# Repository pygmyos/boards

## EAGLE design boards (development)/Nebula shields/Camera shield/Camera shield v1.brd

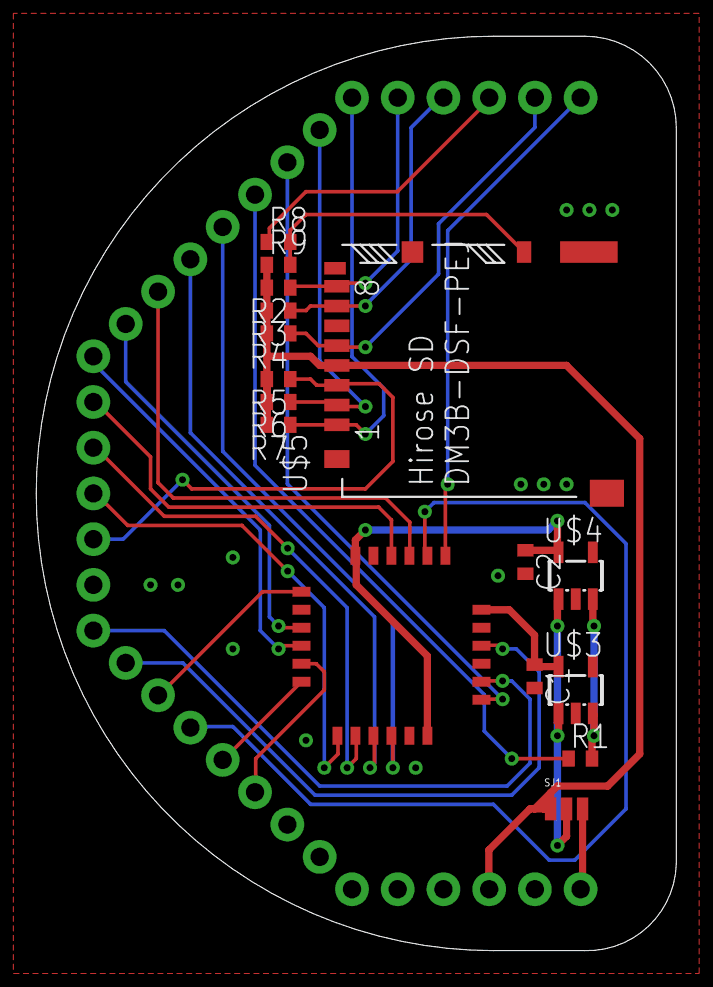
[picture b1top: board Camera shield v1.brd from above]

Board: 2 copper layers, 35.6 x 50.8 mm, 19 parts (1 on the bottom side), 32 nets.

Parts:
C1, C2: 1uF; C0402
INFO2: Evan Teitelman and Warren D Greenway; %CC-NC-SA
LOGO1: #PYGMYLOGONORMAL; #PYGMYLOGO
NEBULA1: #NEBULAPTH; #NEBULA-PTH@1
R1: 1K; R0402
R2, R3, R4, R5, R6, R7: 47K; R0402
R8: 10K; R0402
R9: 100K; R0402
SJ1: SJ_3
U$2: TCM8240MD
U$3, U$4: NCP500; SOT23-5L
U$5: HIROSE-SDCARD-DM3B-DSF-PEJ

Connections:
3.3V: NEBULA1.3.3V, R2.2, R3.2, R4.2, R5.2, R6.2, R7.2, R9.1, SJ1.1, U$5.P$4
BAT: NEBULA1.BAT, SJ1.3
CLK: NEBULA1.COM1_TX, R4.1, U$5.P$5
CMD: NEBULA1.COM2_TX, R5.1, U$5.P$3
D0: NEBULA1.A2, U$2.P4
D1: NEBULA1.A3, U$2.P3
D2: NEBULA1.A4, U$2.P2
D3: NEBULA1.A5, U$2.P1
D4: NEBULA1.A6, U$2.P24
D5: NEBULA1.A7, U$2.P23
D6: NEBULA1.D1, U$2.P22
D7: NEBULA1.D2, U$2.P21
DAT0: NEBULA1.T0, R3.1, U$5.P$7
DAT1: NEBULA1.T1, R2.1, U$5.P$8
DAT2: NEBULA1.T2, R7.1, U$5.P$1
DAT3: NEBULA1.T3, R6.1, U$5.P$2
DCLK: NEBULA1.TA0, U$2.P19
ENABLE: NEBULA1.A1, R1.1
EXTCLK: NEBULA1.MCO, U$2.P13
GND: C1.2, C2.2, NEBULA1.GND1, NEBULA1.GND2, NEBULA1.GND3, NEBULA1.GND4, NEBULA1.GND5, U$2.P5, U$2.P9, U$2.P11, U$2.P17, U$2.P20, U$3.2, U$4.2, U$5.P$6, U$5.P$9, U$5.P$12, U$5.P$13, U$5.P$14
HBLK: NEBULA1.D3, U$2.P15
INSERT: NEBULA1.COM1_RX, R8.1
unnamed: R1.2, U$3.3, U$4.3
unnamed: SJ1.2, U$3.1, U$4.1
unnamed: R8.2, R9.2, U$5.P$11
RST: NEBULA1.A0, U$2.P7
SCL: NEBULA1.DAC1, U$2.P8
SDA: NEBULA1.DAC2, U$2.P10
STROBE: NEBULA1.TA1, U$2.P14
VBLK: NEBULA1.D0, U$2.P16
VCCIO: C1.1, U$2.P12, U$3.5
VDD: C2.1, U$2.P6, U$2.P18, U$4.5

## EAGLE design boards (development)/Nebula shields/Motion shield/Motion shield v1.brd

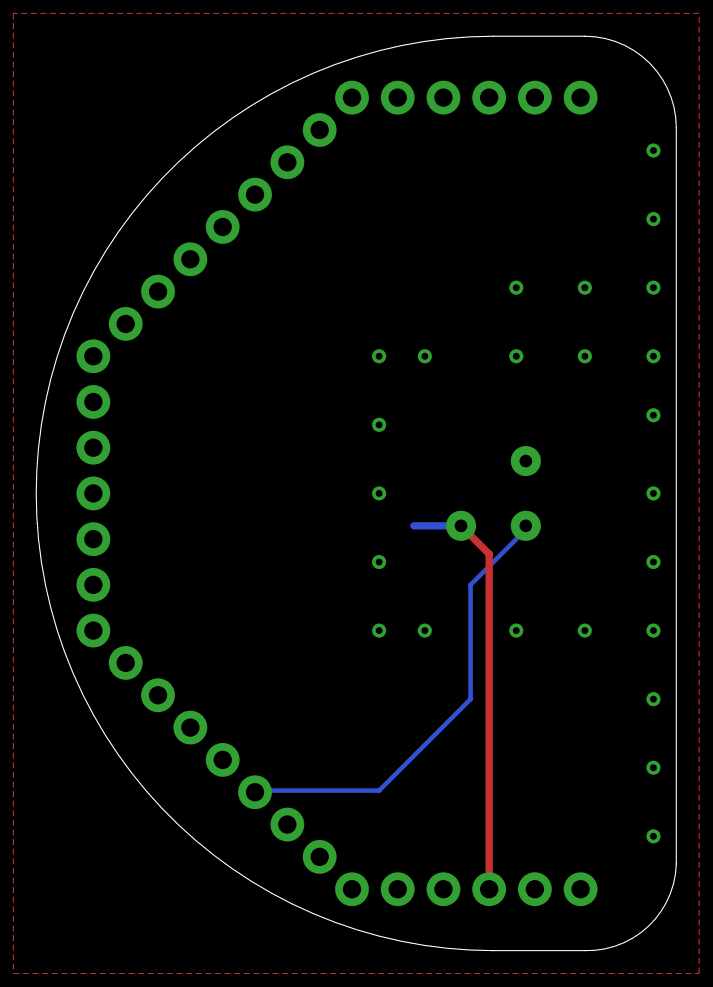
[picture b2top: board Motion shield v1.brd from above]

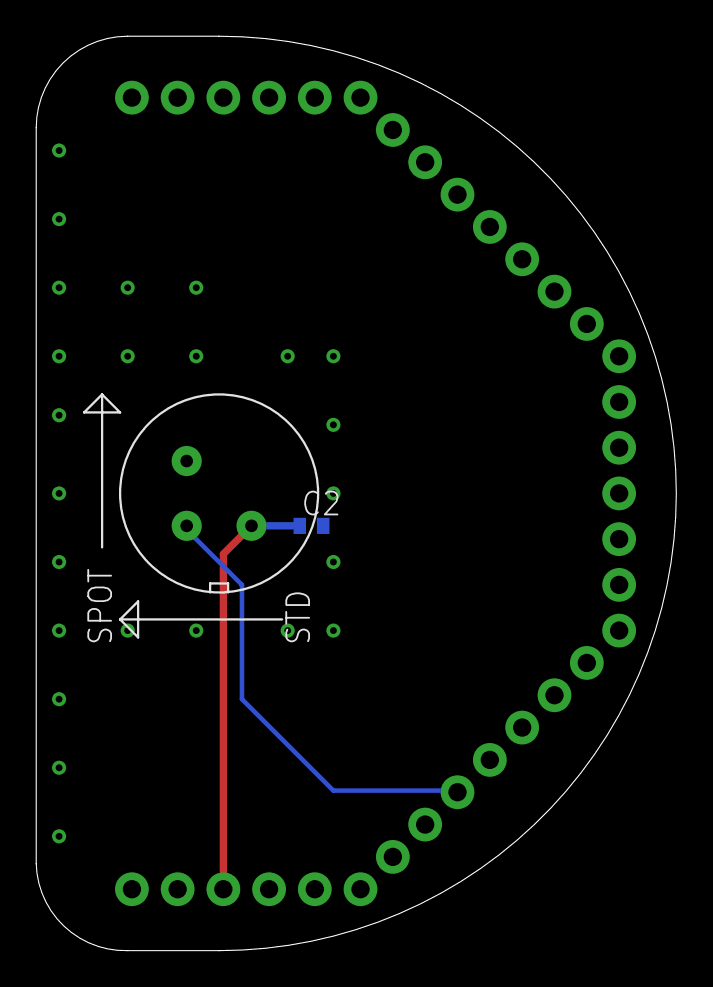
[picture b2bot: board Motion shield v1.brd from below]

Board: 2 copper layers, 35.6 x 50.8 mm, 5 parts (3 on the bottom side), 3 nets.

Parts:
C2: 0.1uF; C0402
INFO2: Warren D Greenway and Evan Teitelman; %CC-NC-SA
LOGO1: #PYGMYLOGONORMAL; #PYGMYLOGO
NEBULA1: #NEBULAPTH; #NEBULA-PTH@1
U2: PANASONIC-AMN41122

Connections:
3.3V: C2.1, NEBULA1.3.3V, U2.VCC
GND: C2.2, NEBULA1.GND1, NEBULA1.GND2, NEBULA1.GND3, NEBULA1.GND4, NEBULA1.GND5, U2.GND
SENSOR: NEBULA1.A7, U2.OUT

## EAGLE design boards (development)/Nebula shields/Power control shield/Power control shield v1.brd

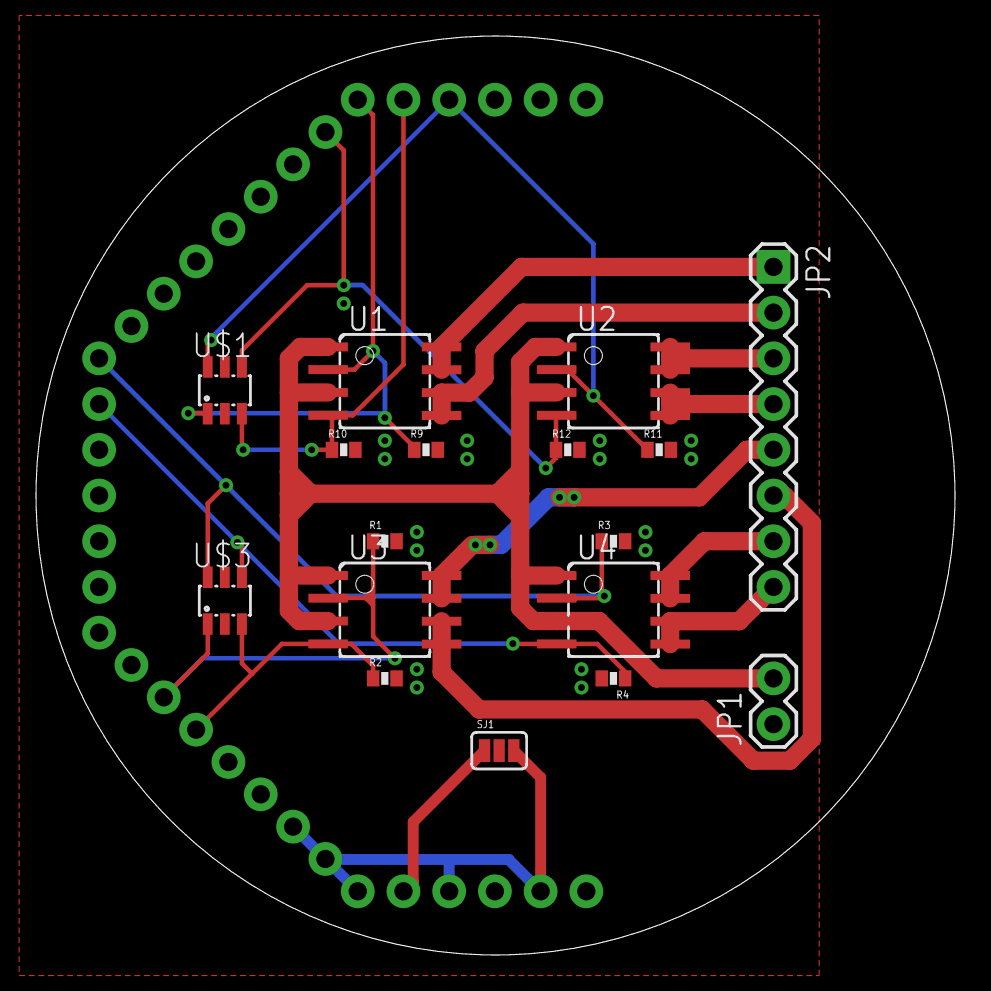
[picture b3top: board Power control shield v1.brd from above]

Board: 2 copper layers, 51.1 x 51.1 mm, 21 parts (1 on the bottom side), 20 nets.

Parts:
INFO2: Evan Teitelman and Warren D Greenway; %CC-NC-SA
JP1: 1X02
JP2: 1X08
LOGO1: #LOGOA-THICK
NEBULA1: #NEBULAPTH; #NEBULA-PTH
NEBULAPART1: #NEBULA-PARTLABELS-BOTTOM; #NEBULA-LABELS-BOTT
R1, R2, R3, R4, R9, R10, R11, R12: 10K; 0402-RES
SJ1: SJ_3_PASTE2&3
U1, U2, U3, U4: TRANSISTOR-VISHAY-SI7288DP; SOIC8
U$1, U$3: ESDAXXSC6; SOT23-6L

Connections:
5V: NEBULA1.5V, SJ1.1
D0: NEBULA1.D0, R4.1, U4.4, U$3.4
D1: NEBULA1.D1, R3.1, U4.2, U$3.6
GND: NEBULA1.GND1, NEBULA1.GND2, NEBULA1.GND3, NEBULA1.GND4, NEBULA1.GND5, SJ1.3
Q1D: JP2.1, U1.7, U1.8
Q2D: JP2.2, U1.5, U1.6
Q3D: JP2.3, U2.7, U2.8
Q4D: JP2.4, U2.5, U2.6
Q5D: JP2.5, U3.7, U3.8
Q6D: JP2.6, U3.5, U3.6
Q7D: JP2.7, U4.7, U4.8
Q8D: JP2.8, U4.5, U4.6
REF: JP1.1, R1.2, R2.2, R3.2, R4.2, R9.2, R10.2, R11.2, R12.2, SJ1.2, U$1.2, U$1.5, U$3.2, U$3.5
T0: NEBULA1.T0, R11.1, U2.2, U$1.6
T1: NEBULA1.T1, R10.1, U1.4, U$1.3
T2: NEBULA1.T2, R9.1, U1.2, U$1.1
T3: NEBULA1.T3, R12.1, U2.4, U$1.4
TA0: NEBULA1.TA0, R1.1, U3.2, U$3.1
TA1: NEBULA1.TA1, R2.1, U3.4, U$3.3
VIN: JP1.2, U1.1, U1.3, U2.1, U2.3, U3.1, U3.3, U4.1, U4.3

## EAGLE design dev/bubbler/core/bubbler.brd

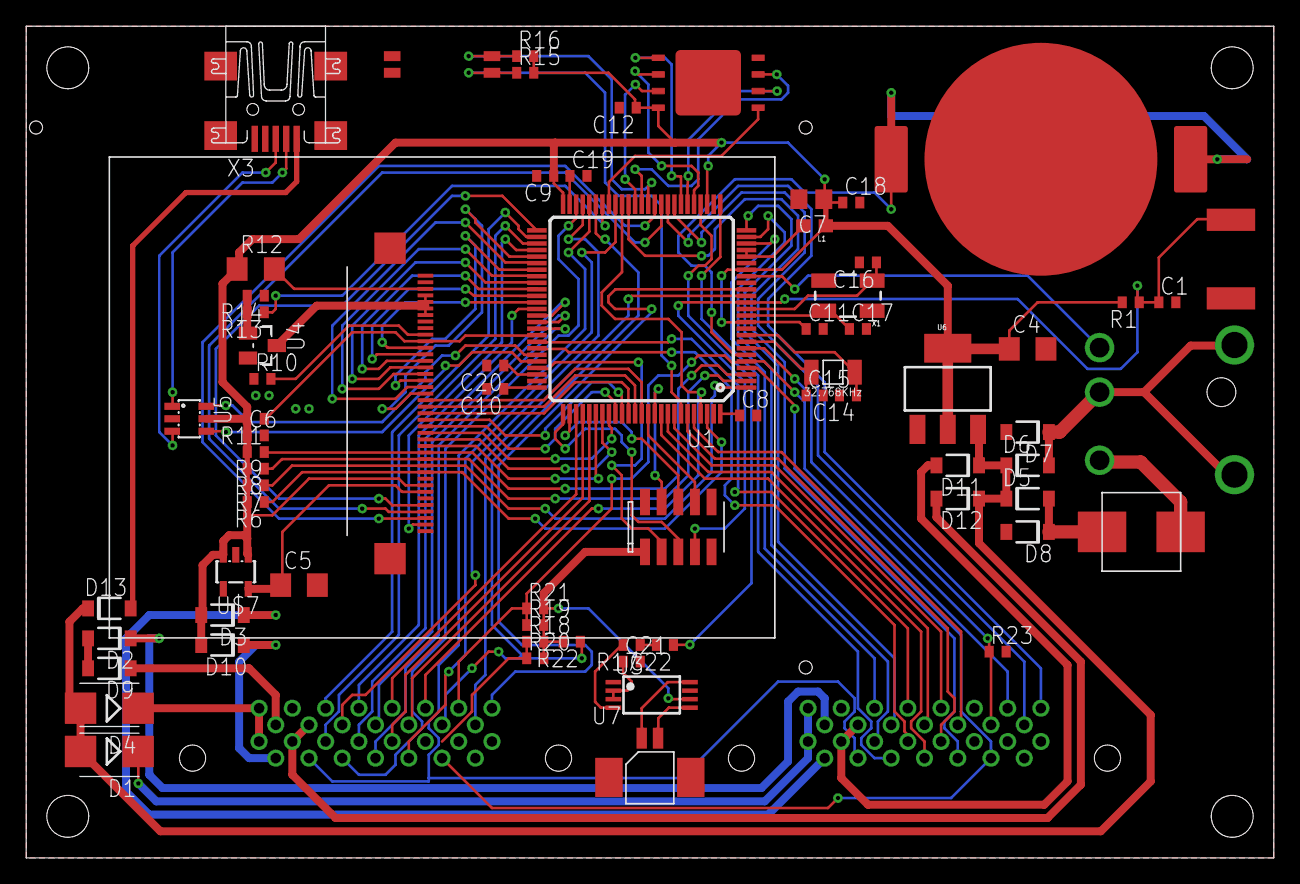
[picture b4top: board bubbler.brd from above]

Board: 2 copper layers, 95.2 x 63.5 mm, 73 parts (0 on the bottom side), 114 nets.

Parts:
B1: BATTERY-LINX-HLD-001
C1: 220pF; C0402
C4, C5: 10uF; C1206
C6, C8, C9, C10, C11, C12, C18, C19, C20: 0.1uF; C0402
C7: 10uF; C0805
C14, C15, C16: 18pF; C0402
C17: 18pf; C0402
C21: 1uF; C0402
C22: 0.39uF; C0402
CARD0, CARD1: CONNECTOR-JAE-TX24-30F; CONNECTOR-JAE-TX24-30
D1, D4: SMB
D2, D3, D5, D6, D7, D8, D9, D10, D11, D12, D13: SMF5.0AT1; SOD123FL
F1: BOURNES-PTC-MF-SMXXXMF-SM030; MF-SM030
L1: 0603
R1, R10, R11, R14, R15, R16, R22, R23: 47K; R0402
R6, R7, R8, R9, R18, R19, R20, R21: 10K; R0402
R12: 330; R1206
R13: 1K; R0402
R17: 20K; R0402
SW1: SWITCH-DIP-GDH-02
SW2: ITT-SWITCH-KSS-G; ITT-KSS-G
U1: STM32F41X-100P; TQFP100
U2: SPANSION-S25FL256; SPANSION-WSON-8
U3: LM4890; TSSOP8
U4: BIPOLAR-PMBT6428; DUBLIB_SOT23
U5: USBLC6-2; SOT23-6L
U6: TLV1117; SOT223
U7: MOLEX-1.25-WTB-RA-CONN-2POS; MOLEX-1.25WTB-RA-CONN
U$1: STM32-JTAG-10P
U$2: DCJACK-CUI-PJ051AH; DCJACK_CUI_PJ012B
U$3: NHD-2.4-240320SF-OUTLINE
U$7: NCP500; SOT23-5L
U$10: NHD-2.4-240320SF; MOLEX-534132-060
X1: CRYSTAL-SMD-5X3
X2: CM415
X3: MINI-USBUX60-MB-5ST; DUBLIB_UX60-MB-5ST

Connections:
2.8V: C5.1, U$7.5, U$10.P34
3.3V: C4.1, C6.1, C7.1, C8.1, C9.1, C10.1, C11.1, C12.1, C18.1, D3.A, D10.A, L1.1, R1.2, R6.2, R7.2, R8.2, R9.2, R11.2, R12.1, R15.2, R16.2, R18.2, R19.2, R20.2, R21.2, R22.2, U1.11, U1.19, U1.28, U1.50, U1.75, U1.100, U2.P8, U3.6, U5.5, U6.2, U6.4, U$1.1, U$7.1, U$7.3, U$10.P33
+5V: D2.A, D9.A
AUDIO_OUT: C22.1, U1.29
BAT: B1.P1, B1.P2, U1.6
BOOT0: R15.1, SW1.P1, U1.94
BOOT1: R16.1, SW1.P2, U1.37
CARD0_INSERT: CARD0.P23, R23.1, U1.7
CARD1_INSERT: CARD1.P23, R22.1, U1.45
CARD_SCL: CARD0.P24, CARD1.P24, R18.1, R20.1, U1.4
CARD_SDA: CARD0.P25, CARD1.P25, R19.1, R21.1, U1.5
EXT0_0: CARD0.P9, U1.23
EXT0_1: CARD0.P10, U1.24
EXT0_2: CARD0.P11, U1.25
EXT0_3: CARD0.P12, U1.26
EXT0_4: CARD0.P13, U1.68
EXT0_5: CARD0.P14, U1.69
EXT0_6: CARD0.P15, U1.92
EXT0_7: CARD0.P16, U1.91
EXT0_8: CARD0.P17, U1.93
EXT0_9: CARD0.P18, U1.95
EXT0_10: CARD0.P19, U1.96
EXT0_11: CARD0.P20, U1.40
EXT0_ADC0: CARD0.P27, U1.33
EXT0_ADC1: CARD0.P29, U1.34
EXT1_0: CARD1.P9, U1.52
EXT1_1: CARD1.P10, U1.53
EXT1_2: CARD1.P11, U1.47
EXT1_3: CARD1.P12, U1.48
EXT1_4: CARD1.P13, U1.63
EXT1_5: CARD1.P14, U1.64
EXT1_6: CARD1.P15, U1.65
EXT1_7: CARD1.P16, U1.66
EXT1_8: CARD1.P17, U1.78
EXT1_9: CARD1.P18, U1.79
EXT1_10: CARD1.P19, U1.80
EXT1_11: CARD1.P20, U1.42
EXT1_12: CARD1.P21, U1.41, U1.97
EXT1_ADC0: CARD1.P27, U1.15
EXT1_ADC1: CARD1.P29, U1.16
FLASH_CS: U1.43, U2.P1
FLASH_IO0: U1.32, U2.P5
FLASH_IO1: U1.31, U2.P2
FLASH_IO2: U1.38, U2.P3
FLASH_IO3: U1.39, U2.P7
FLASH_SCK: U1.30, U2.P6
GND: B1.PAD, C1.2, C4.2, C5.2, C6.2, C7.2, C8.2, C9.2, C10.2, C11.2, C12.2, C14.2, C15.2, C16.2, C17.2, C18.2, C19.2, C20.2, C21.2, CARD0.P5, CARD0.P22, CARD0.P26, CARD0.P28, CARD0.P30, CARD1.P5, CARD1.P22, CARD1.P26, CARD1.P28, CARD1.P30, D7.A, D8.A, R10.1, R14.1, R23.2, SW1.P3, SW1.P4, SW2.P$1, U1.10, U1.20, U1.27, U1.74, U1.99, U2.P4, U3.7, U4.2, U5.2, U6.1, U7.P$3, U7.P$4, U$1.9, U$7.2, U$10.P2, U$10.P8, U$10.P40, X3.4, X3.5, X3.M1, X3.M2, X3.M3, X3.M4
JTCK: U1.76, U$1.5
JTDI: U1.77, U$1.6
JTDO: U1.89, U$1.8
JTMS: U1.72, U$1.3
LCD_BL: R13.1, U1.44
LCD_CS: R6.1, U1.98, U$10.P31
LCD_DB0: U1.81, U$10.P27
LCD_DB1: U1.82, U$10.P26
LCD_DB2: U1.83, U$10.P25
LCD_DB3: U1.84, U$10.P24
LCD_DB4: U1.85, U$10.P23
LCD_DB5: U1.86, U$10.P22
LCD_DB6: U1.87, U$10.P21
LCD_DB7: U1.88, U$10.P20
LCD_DB8: U1.55, U$10.P19
LCD_DB9: U1.56, U$10.P18
LCD_DB10: U1.57, U$10.P17
LCD_DB11: U1.58, U$10.P16
LCD_DB12: U1.59, U$10.P15
LCD_DB13: U1.60, U$10.P14
LCD_DB14: U1.61, U$10.P13
LCD_DB15: U1.62, U$10.P12
LCD_RD: R9.1, U1.3, U$10.P28
LCD_RESET: R11.1, U1.67, U$10.P11
LCD_RS: R7.1, U1.1, U$10.P30
LCD_WR: R8.1, U1.2, U$10.P29
LCD_X+: U1.36, U$10.P38
LCD_X-: U1.51, U$10.P36
LCD_Y+: U1.35, U$10.P37
LCD_Y-: U1.54, U$10.P39
unnamed: CARD1.P4, D10.C
unnamed: D6.A, D7.C, U$2.GND1, U$2.GND2, U$2.P2
unnamed: F1.P$1, U$2.P1
unnamed: R10.2, U$10.P10
unnamed: U5.1, X3.2
unnamed: U5.3, X3.3
unnamed: D5.A, D8.C, F1.P$2
unnamed: R12.2, U$10.P3
unnamed: CARD0.P4, D3.C
unnamed: U4.3, U$10.P4, U$10.P5, U$10.P6, U$10.P7
unnamed: L1.2, U1.21, U1.22
unnamed: C19.1, U1.49
unnamed: R13.2, R14.2, U4.1
unnamed: C20.1, U1.73
unnamed: CARD0.P1, CARD0.P2, D1.C
unnamed: U3.5, U7.P$2
unnamed: U3.8, U7.P$1
unnamed: C21.1, U3.2, U3.3
unnamed: R17.2, U3.4
unnamed: C22.2, R17.1
unnamed: CARD1.P1, CARD1.P2, D4.C
unnamed: CARD0.P3, D2.C
unnamed: CARD0.P6, CARD0.P7, D11.A
unnamed: CARD1.P3, D9.C
unnamed: D13.A, X3.1
unnamed: CARD1.P6, CARD1.P7, D12.A
NJTRST: U1.90, U$1.4
NRST: C1.1, R1.1, SW2.P$2, U1.14, U$1.7
OSC32_IN: C15.1, U1.8, X2.P$2
OSC32_OUT: C14.1, U1.9, X2.P$1
OSC_IN: C17.1, U1.12, X1.3
OSC_OUT: C16.1, U1.13, X1.1
PWR_BAT: CARD0.P8, CARD1.P8, U1.46
PWR_CHG: U1.18, U$2.P3
USB_DM: U1.70, U5.6
USB_DP: U1.71, U5.4
VIN: D1.A, D4.A, D5.C, D6.C, D11.C, D12.C, D13.C, U6.3

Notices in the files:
parts and their libraries:
SparkFun-FreqCtrl: Licensing: CC v3.0 Share-Alike You are welcome to use this library for commercial purposes.
